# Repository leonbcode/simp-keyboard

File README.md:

# SIMP - Simple Macropad

SIMP is a simple macropad designed to optimize task automation. It features a 4x4 key matrix and an OLED display.

## About

SIMP is a hobby project that allows me to learn about microcontrollers and embedded systems. The project aims to create a simple and versatile macropad to enhance productivity. It's important to note that SIMP is a personal project developed for educational purposes. As I'm learning and improving my skills in microcontrollers and embedded systems, SIMP will evolve.

## Features

- 4x4 key matrix 
- OLED display 
- USB-C
- Compact and simple design

## Firmware

I am actively developing a dedicated firmware specifically for SIMP, which can be accessed at [simp-firmware](https://github.com/leonbcode/simp-firmware).

*Please be aware that the firmware is still a work in progress and primarily serves as a learning experience in embedded development.*

## License

This project is licensed under the [MIT License](LICENSE).

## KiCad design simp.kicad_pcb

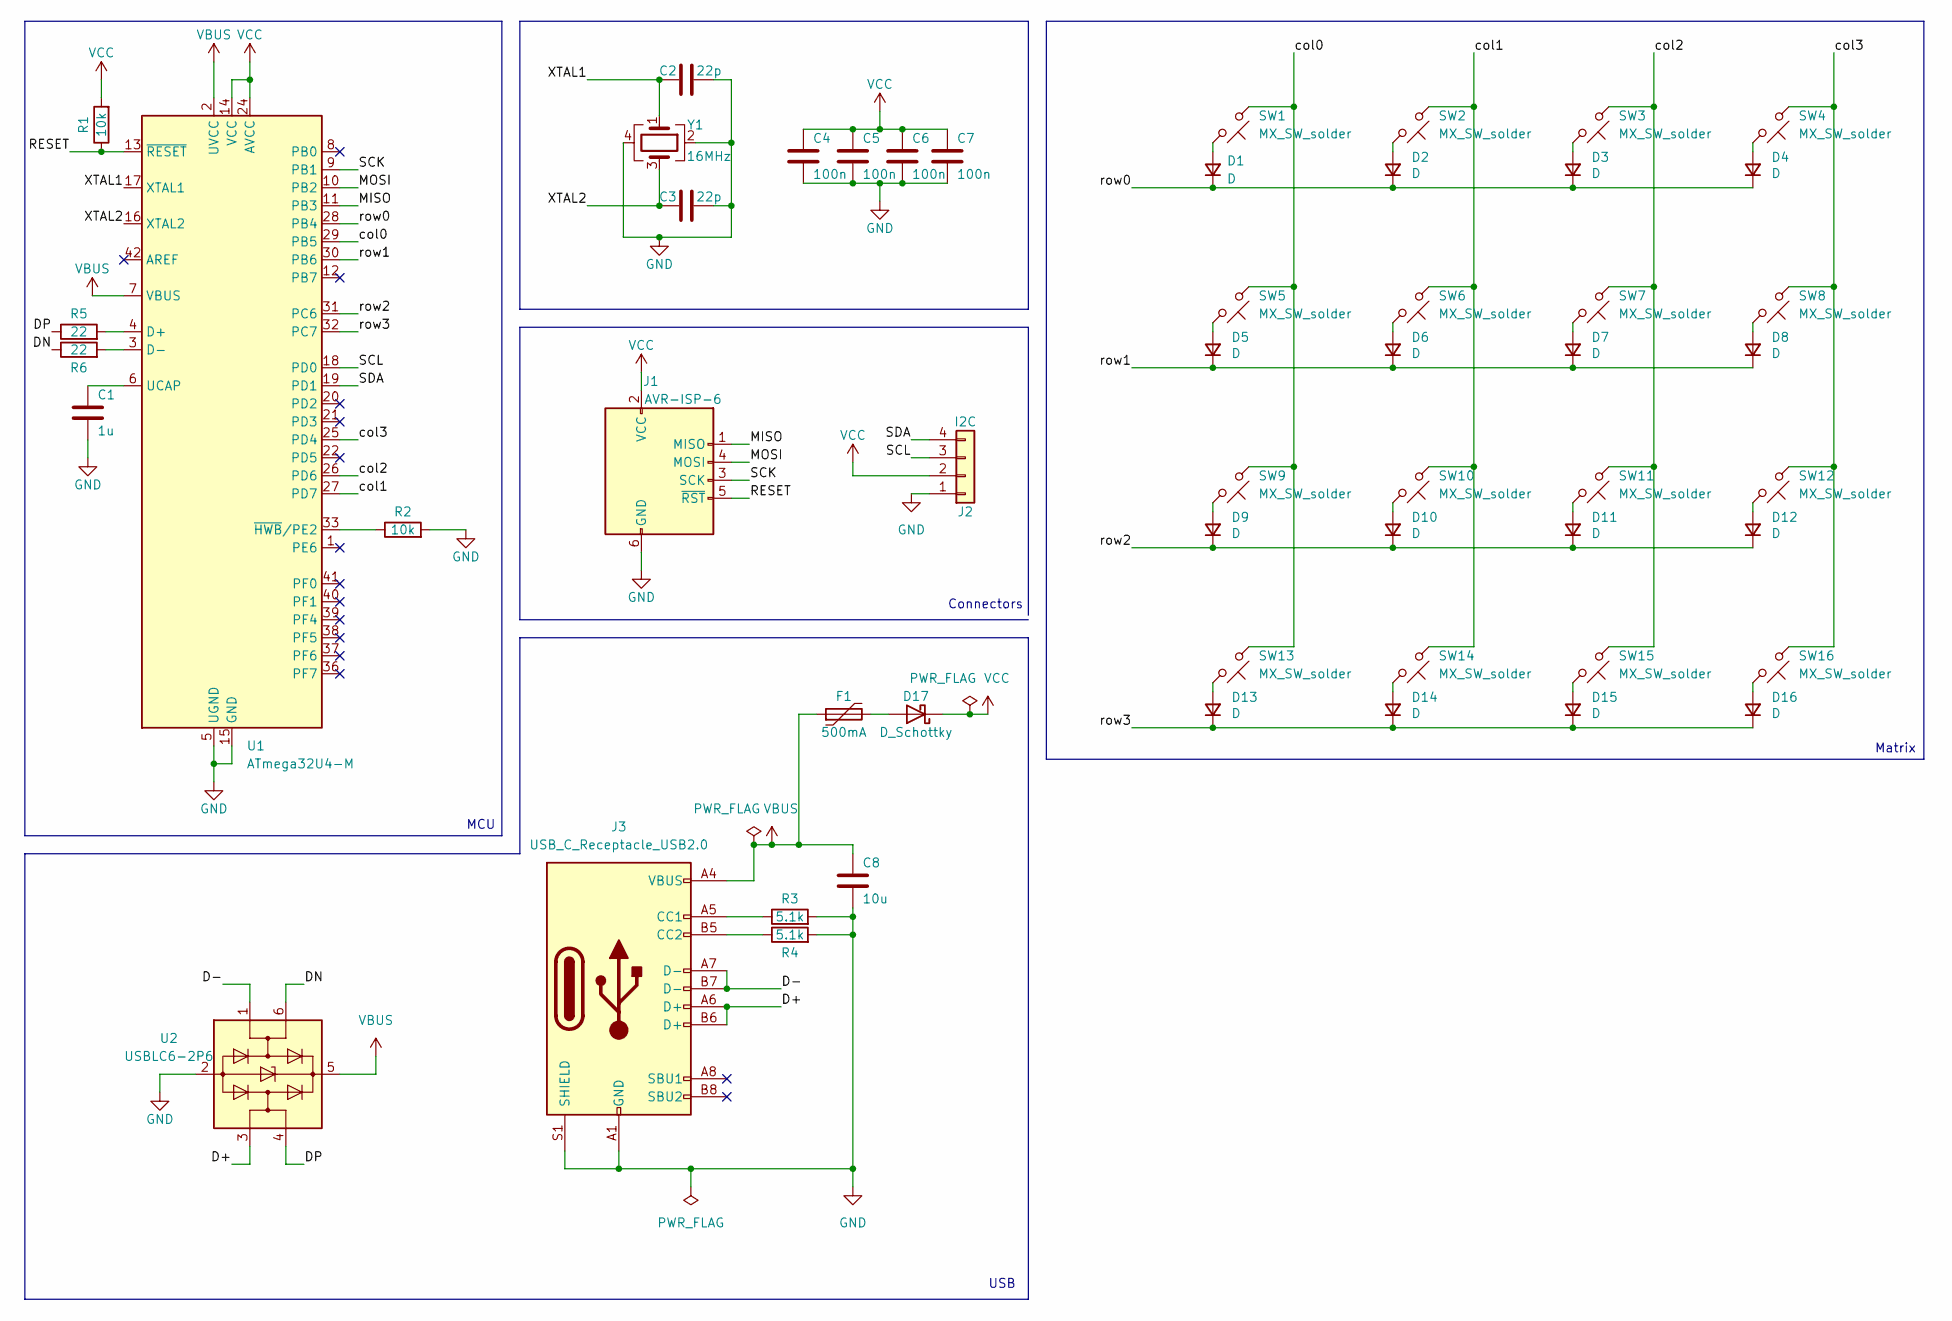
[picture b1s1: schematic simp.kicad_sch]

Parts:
C1: 1u; C_0603_1608Metric
C2, C3: 22p; C_0603_1608Metric
C4, C5, C6, C7: 100n; C_0603_1608Metric
C8: 10u; C_0603_1608Metric
D1, D2, D3, D4, D5, D6, D7, D8, D9, D10, D11, D12, D13, D14, D15, D16: D; D_SOD-123; LCSC C81598
D17: D_Schottky; D_SOD-123F
F1: 500mA; Fuse_0805_2012Metric
J1: AVR-ISP-6; PinSocket_2x03_P2.54mm_Vertical
J2: I2C; PinSocket_1x04_P2.54mm_Vertical
J3: USB_C_Receptacle_USB2.0; USB_C_Receptacle_HRO_TYPE-C-31-M-12
R1, R2: 10k; R_0603_1608Metric
R3, R4: 5.1k; R_0603_1608Metric
R5, R6: 22; R_0603_1608Metric
SW1, SW2, SW3, SW4, SW5, SW6, SW7, SW8, SW9, SW10, SW11, SW12, SW13, SW14, SW15, SW16: MX_SW_solder; SW_MX_1u
U1: ATmega32U4-M; QFN-44-1EP_7x7mm_P0.5mm_EP5.2x5.2mm
U2: USBLC6-2P6; SOT-666
Y1: 16MHz; Crystal_SMD_3225-4Pin_3.2x2.5mm

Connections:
/D+: J3.A6 (D+), J3.B6 (D+), U2.3 (I/O2)
/D-: J3.A7 (D-), J3.B7 (D-), U2.1 (I/O1)
/DN: R6.1, U2.6 (I/O1)
/DP: R5.1, U2.4 (I/O2)
/MISO: J1.1 (MISO), U1.11 (PB3)
/MOSI: J1.4 (MOSI), U1.10 (PB2)
/RESET: J1.5 (~RST), R1.1, U1.13 (~RESET)
/SCK: J1.3 (SCK), U1.9 (PB1)
/SCL: J2.3, U1.18 (PD0)
/SDA: J2.4, U1.19 (PD1)
/XTAL1: C2.1, U1.17 (XTAL1), Y1.1
/XTAL2: C3.1, U1.16 (XTAL2), Y1.3
/col0: SW1.1, SW5.1, SW9.1, SW13.1, U1.29 (PB5)
/col1: SW2.1, SW6.1, SW10.1, SW14.1, U1.27 (PD7)
/col2: SW3.1, SW7.1, SW11.1, SW15.1, U1.26 (PD6)
/col3: SW4.1, SW8.1, SW12.1, SW16.1, U1.25 (PD4)
/row0: D1.1 (K), D2.1 (K), D3.1 (K), D4.1 (K), U1.28 (PB4)
/row1: D5.1 (K), D6.1 (K), D7.1 (K), D8.1 (K), U1.30 (PB6)
/row2: D9.1 (K), D10.1 (K), D11.1 (K), D12.1 (K), U1.31 (PC6)
/row3: D13.1 (K), D14.1 (K), D15.1 (K), D16.1 (K), U1.32 (PC7)
GND: C1.2, C2.2, C3.2, C4.2, C5.2, C6.2, C7.2, C8.2, J1.6 (GND), J2.1, J3.A1 (GND), J3.A12 (GND), J3.B1 (GND), J3.B12 (GND), J3.S1 (SHIELD), R2.2, R3.2, R4.2, U1.5 (UGND), U1.15 (GND), U1.23 (GND), U1.35 (GND), U1.43 (GND), U1.45 (GND), U2.2 (GND), Y1.2, Y1.4
unnamed: C1.1, U1.6 (UCAP)
unnamed: D1.2 (A), SW1.2
unnamed: D2.2 (A), SW2.2
unnamed: D3.2 (A), SW3.2
unnamed: D4.2 (A), SW4.2
unnamed: D5.2 (A), SW5.2
unnamed: D6.2 (A), SW6.2
unnamed: D7.2 (A), SW7.2
unnamed: D8.2 (A), SW8.2
unnamed: D9.2 (A), SW9.2
unnamed: D10.2 (A), SW10.2
unnamed: D11.2 (A), SW11.2
unnamed: D12.2 (A), SW12.2
unnamed: D13.2 (A), SW13.2
unnamed: D14.2 (A), SW14.2
unnamed: D15.2 (A), SW15.2
unnamed: D16.2 (A), SW16.2
unnamed: D17.2 (A), F1.2
unnamed: J3.A5 (CC1), R3.1
unnamed: J3.B5 (CC2), R4.1
unnamed: R2.1, U1.33 (~HWB/PE2)
unnamed: R5.2, U1.4 (D+)
unnamed: R6.2, U1.3 (D-)
VBUS: C8.1, F1.1, J3.A4 (VBUS), J3.A9 (VBUS), J3.B4 (VBUS), J3.B9 (VBUS), U1.2 (UVCC), U1.7 (VBUS), U2.5 (VBUS)
VCC: C4.1, C5.1, C6.1, C7.1, D17.1 (K), J1.2 (VCC), J2.2, R1.2, U1.14 (VCC), U1.24 (AVCC), U1.34 (VCC), U1.44 (AVCC)

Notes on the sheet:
Matrix
Connectors
USB
MCU

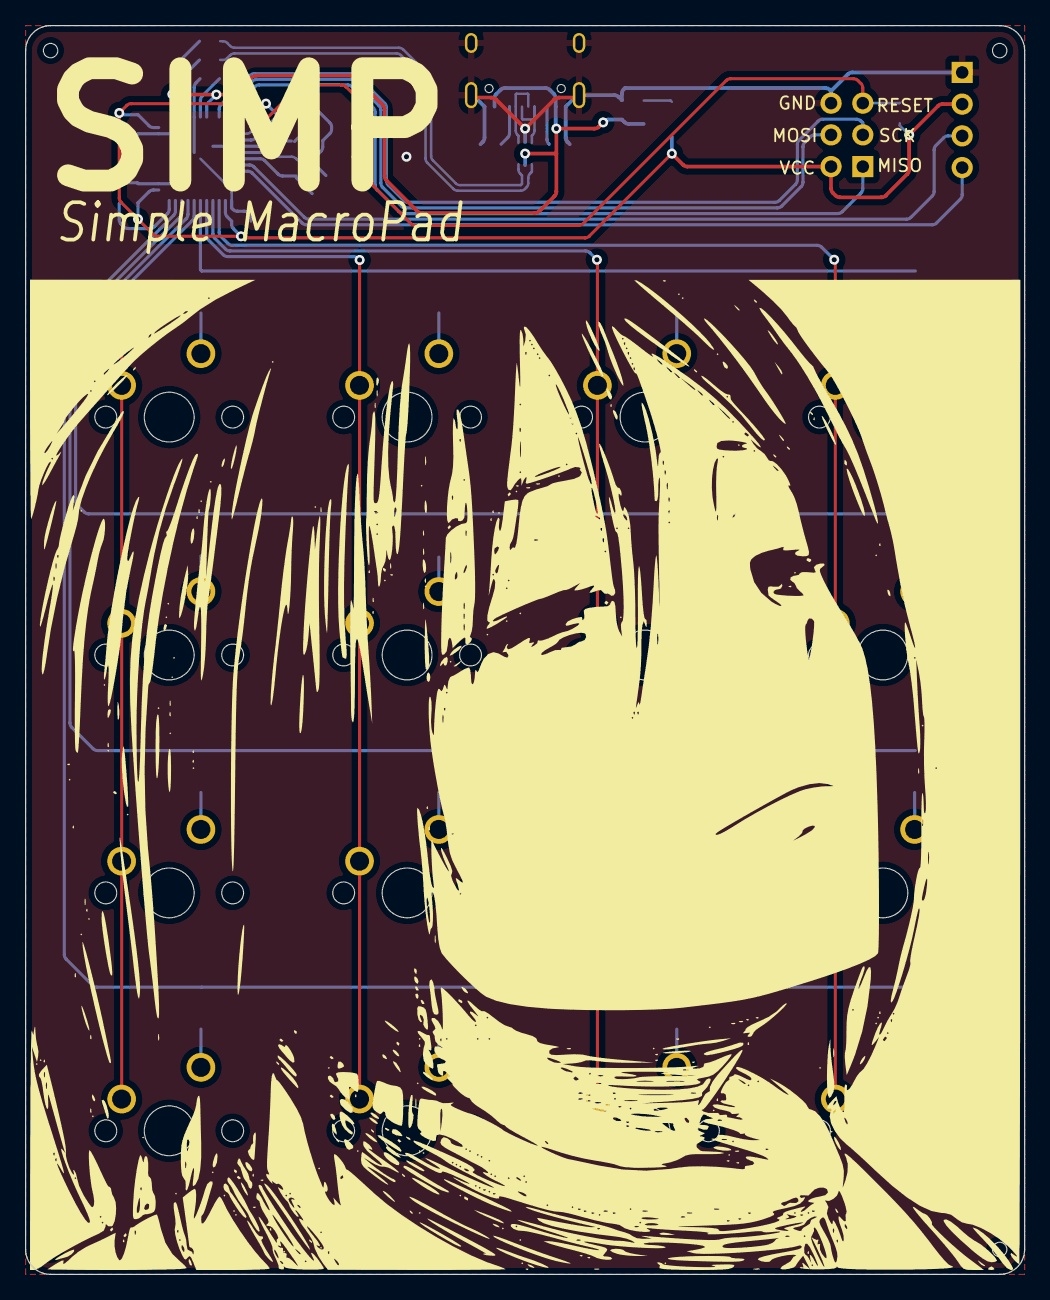
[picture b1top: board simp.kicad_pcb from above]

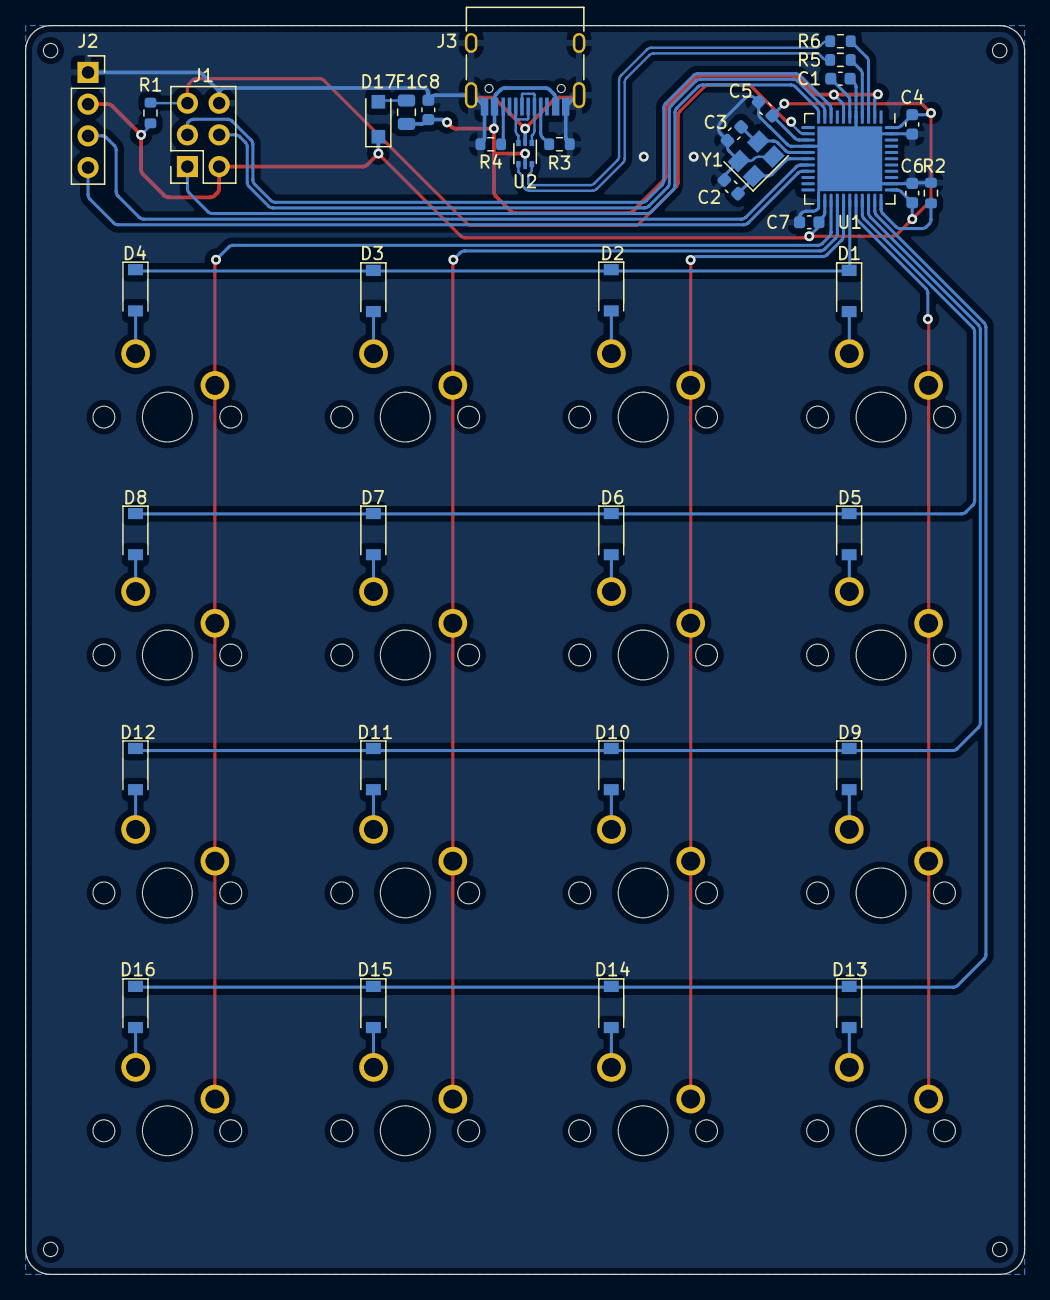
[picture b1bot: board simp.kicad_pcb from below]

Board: 2 copper layers, 80.0 x 100.0 mm, 54 parts (38 on the bottom side), 46 nets.

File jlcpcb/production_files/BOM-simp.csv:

Comment,Designator,Footprint,LCSC
ATmega32U4-M,U1,QFN-44-1EP_7x7mm_P0.5mm_EP5.2x5.2mm,C112161
16MHz,Y1,Crystal_SMD_3225-4Pin_3.2x2.5mm,C13738
1u,C1,C_0603_1608Metric,C15849
100n,"C4,C5,C6,C7",C_0603_1608Metric,C1591
22p,"C2,C3",C_0603_1608Metric,C1653
USB_C_Receptacle_USB2.0,J3,USB_C_Receptacle_HRO_TYPE-C-31-M-12,C165948
D_Schottky,D17,D_SOD-123F,C169540
10u,C8,C_0603_1608Metric,C19702
22,"R5,R6",R_0603_1608Metric,C22775
5.1k,"R3,R4",R_0603_1608Metric,C23186
10k,"R1,R2",R_0603_1608Metric,C25804
500mA,F1,Fuse_0805_2012Metric,C269104
USBLC6-2P6,U2,SOT-666,C2827693
D,"D1,D10,D11,D12,D13,D14,D15,D16,D2,D3,D4,D5,D6,D7,D8,D9",D_SOD-123,C81598
MX_SW_solder,SW7,SW_MX_1u,
MX_SW_solder,SW12,SW_MX_1u,
MX_SW_solder,SW11,SW_MX_1u,
MX_SW_solder,SW15,SW_MX_1u,
MX_SW_solder,SW5,SW_MX_1u,
MX_SW_solder,SW1,SW_MX_1u,
MX_SW_solder,SW9,SW_MX_1u,
MX_SW_solder,SW16,SW_MX_1u,
MX_SW_solder,SW3,SW_MX_1u,
MX_SW_solder,SW4,SW_MX_1u,
MX_SW_solder,SW6,SW_MX_1u,
MX_SW_solder,SW2,SW_MX_1u,
MX_SW_solder,SW10,SW_MX_1u,
MX_SW_solder,SW14,SW_MX_1u,
MX_SW_solder,SW8,SW_MX_1u,
MX_SW_solder,SW13,SW_MX_1u,
I2C,J2,PinSocket_1x04_P2.54mm_Vertical,
AVR-ISP-6,J1,PinSocket_2x03_P2.54mm_Vertical,

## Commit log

2023-05-16 add project files
2023-05-16 fix: add sumbodule
2023-05-16 license: add MIT license
2023-05-16 doc: update README
2023-05-16 version: bump version to 1.0.0
